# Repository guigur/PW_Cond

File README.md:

# PW_Cond
Conditionneur de pont de wheatstone

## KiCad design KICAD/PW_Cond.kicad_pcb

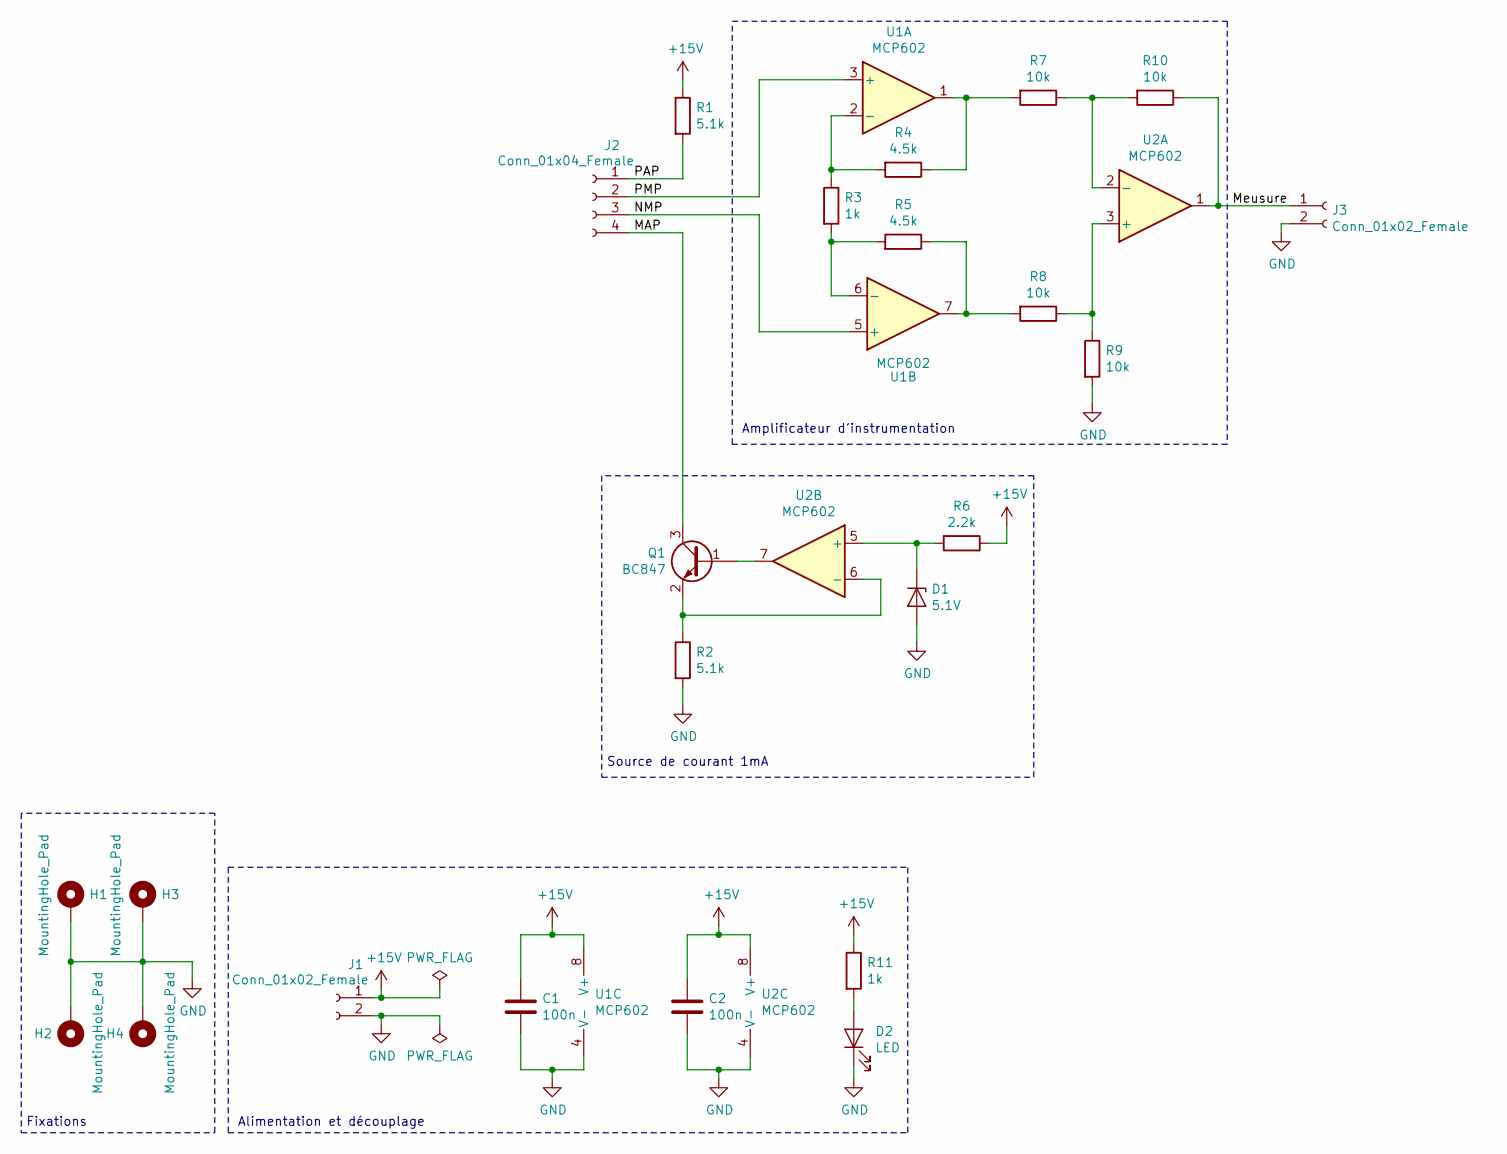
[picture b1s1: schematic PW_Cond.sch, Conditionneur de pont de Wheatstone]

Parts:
C1, C2: 100n; C_0805_2012Metric_Pad1.15x1.40mm_HandSolder
D1: 5.1V; D_SOD-123
D2: LED; LED_D3.0mm
H1, H2, H3, H4: MountingHole_Pad; MountingHole_2.2mm_M2_Pad_Via
J1, J3: Conn_01x02_Female; PinHeader_1x02_P2.54mm_Vertical
J2: Conn_01x04_Female; PinHeader_1x04_P2.54mm_Vertical
Q1: BC847; SOT-23
R1, R2: 5.1k; R_0805_2012Metric_Pad1.15x1.40mm_HandSolder
R3, R11: 1k; R_0805_2012Metric_Pad1.15x1.40mm_HandSolder
R4, R5: 4.5k; R_0805_2012Metric_Pad1.15x1.40mm_HandSolder
R6: 2.2k; R_0805_2012Metric_Pad1.15x1.40mm_HandSolder
R7, R8, R9, R10: 10k; R_0805_2012Metric_Pad1.15x1.40mm_HandSolder
U1, U2: MCP602; SOIC-8_3.9x4.9mm_P1.27mm

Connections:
+15V: C1.1, C2.1, J1.1, R1.1, R6.1, R11.1, U1.8 (V+), U2.8 (V+)
/MAP: J2.4, Q1.3 (C)
/Meusure: J3.1, R10.1, U2.1
/NMP: J2.3, U1.5 (+)
/PAP: J2.1, R1.2
/PMP: J2.2, U1.3 (+)
GND: C1.2, C2.2, D1.2 (A), D2.1 (K), H1.1, H2.1, H3.1, H4.1, J1.2, J3.2, R2.2, R9.2, U1.4 (V-), U2.4 (V-)
unnamed: D1.1 (K), R6.2, U2.5 (+)
unnamed: D2.2 (A), R11.2
unnamed: Q1.1 (B), U2.7
unnamed: Q1.2 (E), R2.1, U2.6 (-)
unnamed: R3.1, R4.2, U1.2 (-)
unnamed: R3.2, R5.2, U1.6 (-)
unnamed: R4.1, R7.2, U1.1
unnamed: R5.1, R8.2, U1.7
unnamed: R8.1, R9.1, U2.3 (+)
unnamed: R7.1, R10.2, U2.2 (-)

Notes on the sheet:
Amplificateur d’instrumentation
Source de courant 1mA
Alimentation et découplage
Fixations

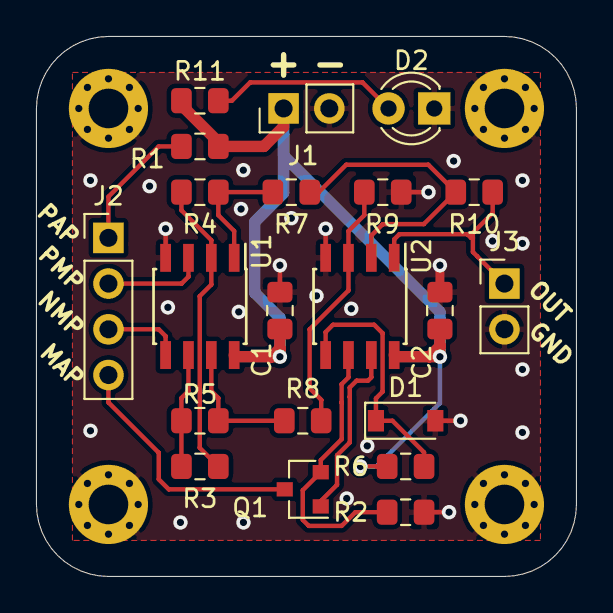
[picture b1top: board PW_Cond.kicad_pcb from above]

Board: 2 copper layers, 30.0 x 30.0 mm, 26 parts (1 on the bottom side), 17 nets.

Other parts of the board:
S1: KiCad-Logo2_6mm_SilkScreen

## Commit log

2021-07-27 first version
2021-07-27 correct ampli op + tied up
2021-07-27 added footprints and an LED git add *
2021-07-27 minor cleanup + started pcb
2021-07-27 psb is going well
2021-07-28 placement seems to be finished
2021-07-28 board v1 finished
2021-07-28 kicad logo + minor tweaks
2021-07-28 tweaks on signals + vias
2021-07-29 Mod serigraphie
2021-07-29 cleanup + fab files wip
